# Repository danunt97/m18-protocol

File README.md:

# M18 Akku-Verwaltung

Mit diesem Tool **liest du Milwaukee-M18-Akkus aus, verwaltest sie in einer Datenbank und verfolgst ihre Alterung**.
Das Programm läuft als lokaler Webserver auf dem eigenen PC, ohne Installation und ohne Cloud. Auf Wunsch übernimmt
eine **ESP32-S3-Brücke** das Auslesen per WLAN oder direkt vor Ort mit dem Handy.

Das Projekt baut auf der Protokoll-Forschung von [mnh-jansson/m18-protocol](https://github.com/mnh-jansson/m18-protocol) auf.

## Funktionen

**Akku-Verwaltung (PC, `gui/`)**
- **Auslesen** über einen 3,3-V-USB-Seriell-Adapter oder die ESP32-Brücke. Bekannte Akkus erkennt das Programm automatisch, neue legt es mit einem Klick an.
- **Datenbank (SQLite):** jede Messung mit Zeitstempel, allen Zählern und den rohen Registerwerten.
- **Flottenübersicht:** Zustand, Verlauf, Trend, Zell-Imbalance, Zyklen, Standort, fällige Messungen und offene Warnungen. Die Liste lässt sich filtern und sortieren.
- **Alterung:** Diagramme pro Akku und eine Prognose, wann der Akku schwach wird.
- **Warnungen**, wenn sich ein Akku deutlich verschlechtert: Zustandsabfall, steigende Imbalance, neue Überhitzungs- oder Unterspannungs-Ereignisse, Ladung mit einer Zelle unter 2,5 V.
- **Standort, Kommentar und Gehäuse-Seriennummer** sind editierbar; Akkus lassen sich ausmustern.
- **QR-Etiketten** für P-touch (12–36 mm) und Brother QL (62 mm). Der QR-Code führt direkt zur Akku-Seite, der Code wird offline erzeugt.
- **Berichte:** druckbare A4-Seite bzw. PDF pro Akku, CSV pro Akku oder für die ganze Flotte, Datenbank-Backup.
- **Demo-Modus** mit 8 simulierten Akkus und 2 Jahren Verlauf, ganz ohne Hardware.

**ESP32-S3-Akku-Brücke (`esp32-bridge/`)**
- **Ersetzt den USB-Seriell-Adapter.** Der PC verbindet sich per USB oder WLAN und findet die Brücke im Netz automatisch.
- **Eigene Weboberfläche fürs Handy:**
  - Akku direkt auslesen, mit Zustand, Zellspannungen, Zählern und Daten
  - WLAN-Einrichtung beim Kunden (Captive Portal)
  - Verlauf, Status-LED, Firmware-Update im Browser
- **Messungen offline speichern** (mehrere tausend im Flash) und später **in die PC-Datenbank übernehmen**. Dafür werden die Rohregister gespeichert; eine übernommene Messung ist gleichwertig mit einer am PC.
- **Robust:**
  - Wiederholungen und schneller Abbruch bei gezogenem Akku
  - Watchdog
  - J2 bleibt im Ruhezustand sicher auf Low, damit der Akku keine „Dumb Charge“ zählt
- **Optionaler Passwortschutz.** Einstellungen ändern geht nur nach einem Druck auf die BOOT-Taste.
- **Aufsteckgehäuse zum 3D-Drucken**, Versorgung aus dem Akku, **Energiesparmodus** (Tiefschlaf nach Ruhezeit).
- **Ergebnis auf der LED:** Nach jedem Auslesen leuchtet sie 30 s grün, gelb oder rot, auch wenn der PC ausliest.
- **Firmware im Browser installieren** (ESP Web Tools), ganz ohne Arduino IDE.
- **Cloud (Supabase):** Konto, „Meine Akkus“ mit Verlauf. Jede Messung landet komplett in der Cloud, aus der App oder direkt von der Brücke, wenn sie im WLAN Internet hat.
- **Bluetooth fürs Handy:** Die [Akku-App](https://akkuscan.app/) läuft im Browser (Android: Chrome, iPhone: kostenlose App „Bluefy“).
  Ohne WLAN-Wechsel: Akku auslesen, alle Werte, Verlauf und Protokoll der Brücke. Keine App-Store-App und kein Entwicklerkonto nötig.

**Betrieb auf dem NAS:** Docker-Image mit **automatischem Abgleich**. Die Messungen der Brücken landen von selbst in der Datenbank.

## Bilder

| Akku-Detail mit Alterungsverlauf | Auslesen und Vergleich mit der letzten Messung |
|---|---|
|  |  |
| **QR-Etiketten (P-touch 24 mm)** | **Druckbarer Bericht** |
|  |  |

**ESP32-Brücke am Handy:** WLAN einrichten, Akku auslesen, gespeicherte Messungen

**Messungen der Brücke in die PC-Datenbank übernehmen**

> Alle Bilder stammen aus dem Demo-Modus bzw. aus dem Simulator. Die Messwerte sind simuliert.

## Schnellstart

Du brauchst **Python 3.11 oder neuer**. Weitere Pakete braucht die Demo nicht.

```bash
git clone https://github.com/danunt97/m18-protocol.git
```

```bash
cd m18-protocol
```

```bash
python gui/m18_gui.py --demo
```

Danach öffnet sich der Browser mit http://127.0.0.1:8018. Unter Windows startest du mit `py gui\m18_gui.py --demo`.

**Mit echtem Akku:**

```bash
pip install pyserial
```

```bash
python gui/m18_gui.py
```

Dann **Auslesen** → Adapter wählen → **Verbinden** → **Akku auslesen** → speichern.
Die Datenbank liegt in `data/m18_fleet.db`.

Alle Optionen (`--host 0.0.0.0` für Handy-Scans im WLAN, `--db`, `--port` …) stehen in [gui/README.md](gui/README.md).

**Dauerhaft auf dem NAS / Server (Docker):**

```bash
docker compose up -d
```

Dann ist die Oberfläche unter `http://<NAS-IP>:8018` erreichbar. Die Datenbank liegt in `./data`, und Messungen der ESP32-Brücken
werden **automatisch alle 5 Minuten übernommen**. Das Image (`ghcr.io/danunt97/m18-protocol`) gibt es für amd64 und arm64;
Details stehen in [gui/README.md](gui/README.md#docker).

## Hardware

Es gibt zwei Möglichkeiten, den Akku anzuschließen:

1. **3,3-V-USB-Seriell-Adapter** wie im ursprünglichen Projekt. Verdrahtung und Fehlersuche stehen in [docs/m18-protocol.md](docs/m18-protocol.md).
2. **ESP32-S3 (N16R8) als Brücke.** Das bringt WLAN, Messen ohne PC und eine eigene Weboberfläche. Am bequemsten ist das
   **3D-gedruckte Aufsteckgehäuse**: Es wird wie ein Werkzeug auf den Akku geschoben und versorgt die Elektronik über einen
   Step-down-Wandler aus dem Akku. Druckdateien, Stückliste und Zusammenbau stehen in [hardware/aufsteckgehaeuse/](hardware/aufsteckgehaeuse/README.md).

| Aufsteckgehäuse | Elektronik im Gehäuse |
|---|---|
|  |  |

**Firmware ohne Arduino IDE installieren:** Die Seite **[akkuscan.app/flasher](https://akkuscan.app/flasher/)**
öffnen (Chrome oder Edge), das Board per USB anstecken und auf **Installieren** klicken.

Oder mit der Arduino IDE 2 flashen. Ins Werkzeuge-Menü gehören diese Einstellungen:
- Board: **ESP32S3 Dev Module**
- Flash: **16MB**
- PSRAM: **OPI**
- Partition: **16M Flash (3MB APP/9.9MB FATFS)**
- USB CDC On Boot: **Enabled**

Danach `esp32-bridge/m18_bridge/m18_bridge.ino` hochladen. Alles Weitere zu WLAN-Einrichtung, LED, Passwort und Update
steht in [esp32-bridge/README.md](esp32-bridge/README.md).

> ⚠️ **Sicherung (T 500 mA) direkt hinter B+ einbauen** und den **Step-down vor dem ersten Anschließen auf 5,0 V einstellen.** Solange das Gehäuse steckt, versorgt der Akku die Elektronik.
> Die Brücke schläft deshalb nach 30 min Ruhe (BOOT-Taste weckt sie); nach Gebrauch abziehen.
>
> ⚠️ **Sicherheit:** Arbeiten an Li-Ion-Akkus auf eigene Gefahr. Die ESP32-Brücke kann nur lesen und die
> 20-Zeichen-Notiz im Akku schreiben. Zähler, Kalibrierung oder Firmware des Akkus fasst sie nicht an.

## Wie wird der Zustand bewertet?

Der Akku speichert keinen echten State-of-Health. Die Software **schätzt** ihn aus den Verschleißzählern im Akku:
100 Punkte minus Abzüge für
- Zyklen (entladene Ah ÷ Nennkapazität)
- Zell-Imbalance
- Ladungen mit einer Zelle < 2,5 V
- Überhitzung
- Kalenderalter

Jeder Abzug wird einzeln angezeigt.
Aussagekräftig ist vor allem der **Verlauf über mehrere Messungen**. Details und Warnschwellen findest du in [gui/README.md](gui/README.md).

## Projektstruktur

```
m18.py                  Protokoll und Kommandozeile (aus m18-protocol)
m18_bridge.py           ESP32-Brücke als M18-Objekt (USB/WLAN), Suche, Abgleich
gui/                    Akku-Verwaltung: Webserver, Datenbank, Alterung, QR, Berichte
  m18_gui.py            Start: python gui/m18_gui.py [--demo]
  fleet.py              SQLite, Zustandsschätzung, Warnungen, Trend
  registers.py          Register → Messwerte (Live und Import identisch)
  bridge_import.py      Messungen der Brücke übernehmen
  qrgen.py              QR-Code-Encoder (reines Python)
  static/               Oberfläche (HTML/CSS/JS, ohne Framework)
webble/                 Bluetooth-Adapter: macht die Weboberfläche der Brücke zur Handy-App (akkuscan.app/app/)
supabase/               Cloud-Datenbank (Schema, Zugriffsregeln, Upload-Funktionen)
esp32-bridge/
  m18_bridge/           Arduino-Sketch + reine C++-Header (Protokoll, Auslesen, Speicher)
  test/                 Simulator und Ende-zu-Ende-Tests
hardware/aufsteckgehaeuse/  3D-Druck-Gehäuse (3MF, STL, Fusion 360), Stückliste, Zusammenbau
docs/                   Bilder, ursprüngliche Protokoll-Doku, Register-Tabelle
```

## Tests

Die Tests laufen ohne Hardware: Ein simulierter Akku spricht das echte Protokoll, und der C++-Kern der Firmware wird
auf dem PC mitgetestet. GitHub Actions führt sie bei jedem Push aus und **kompiliert die Firmware für den ESP32-S3**
mit den Arduino-Cores 2.x und 3.x.

```bash
python -m unittest discover -s gui/tests
```

```bash
g++ -std=c++17 -I esp32-bridge/m18_bridge esp32-bridge/test/sim_bridge.cpp -o sim_bridge
```

```bash
./sim_bridge test
```

```bash
python -m unittest esp32-bridge/test/test_bridge.py esp32-bridge/test/test_history.py
```

Die Brücken-Tests über USB brauchen `pyserial`, alles andere nur die Standardbibliothek.

## Grundlage und Hinweise

- Protokoll, Registertabelle und `m18.py` stammen aus [mnh-jansson/m18-protocol](https://github.com/mnh-jansson/m18-protocol)
  und der Community dort. Die ursprüngliche Anleitung liegt in [docs/m18-protocol.md](docs/m18-protocol.md).
- Kein offizielles Milwaukee-Produkt. „Milwaukee“ und „M18“ sind Marken ihrer jeweiligen Inhaber.
- Änderungen stehen im [CHANGELOG](CHANGELOG.md).

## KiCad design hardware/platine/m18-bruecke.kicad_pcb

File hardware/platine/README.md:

# Platine: M18-Brücke mit ESP32-S3 SuperMini

Eigene Leiterplatte für die [Akku-Brücke](../../esp32-bridge/README.md). Die fünf Akkukontakte sitzen direkt auf der Platine. Der SuperMini wird mit seinen mitgelieferten Stiftleisten direkt eingelötet. Der Pegelwandler ist durch zwei kleine Transistorstufen ersetzt, der
Step-down-Wandler durch einen RECOM-Schaltregler. Alles ist von Hand lötbar (SMD ab 0805 / SOT-23 / SMA).

| Oben | Unten (Akkuseite) |
|---|---|
|  |  |

> **Stellen mit ⚠ PRÜFEN** beruhen auf Annahmen, weil Datenblatt, Pinbelegung oder Foto beim Entwurf fehlten.
> Bitte vor der Bestellung der 20 Platinen kontrollieren (Liste ganz unten).

## Eckdaten

| | |
|---|---|
| Größe | **58 × 38 mm**, 2 Lagen, 1,6 mm, 35 µm Kupfer |
| Befestigung | 4 × **M3** (Bohrung 3,2 mm), Mitte 4 mm von den Kanten, Lochabstand **50 × 30 mm** |
| Akkukontakte | 5 × TE **928814-1** (FASTON 6,35 × 0,81 mm) im Raster **5,625 mm** auf der **Unterseite**. Lötstifte am linken Rand, die Messer zeigen unter die Platine, die damit über dem Akku liegt |
| Versorgung | aus dem Akku (B+ 15–21 V) oder über USB-C des SuperMini |
| Ruhestrom aus B+ | nur der Eigenverbrauch des Reglers (R-78E, Wert im Datenblatt nachsehen und am Muster messen) und der Schlafstrom des ESP. Die J2-Stufe zieht im Ruhezustand nichts. |
| Laden | vorbereitet: Lötlöcher CHG+/CHG− für 1,5-mm²-Litze und 6-poliger Steuerstecker, nichts bestückt |

Bezugspunkt aller Maße ist die linke obere Ecke der Draufsicht (x nach rechts = Richtung der Messerspitzen = Einsteckrichtung, y nach unten).

## Akkukontakte

Draufsicht, Lötstifte am linken Rand, Messerspitzen zeigen nach rechts unter die Platine:

| Kontakt | Bauteil | Mitte y | Abstand zum Nachbarn |
|---|---|---|---|
| **B+** | X1 | 7,750 mm | – |
| **J1** | X2 | 13,375 mm | 5,625 mm |
| **M** (Mitte) | X5 | 19,000 mm | 5,625 mm |
| **J2** | X3 | 24,625 mm | 5,625 mm |
| **B−** | X4 | 30,250 mm | 5,625 mm |

- Von oben in Einsteckrichtung gesehen (Spitzen zeigen von dir weg): **links B+, J1, M, J2, rechts B−**. In der Draufsicht oben ist deshalb B+.
- Raster 5,625 mm von Mitte zu Mitte, wie in der Skizze des Printables-Modells „Milwaukee M18 All Pins“. Die Platinenmitte (y = 19) ist der mittlere Kontakt.
- Der **mittlere Kontakt M** (X5) ist mit nichts verbunden, er führt nur auf das Lötfeld **TP3** zwischen seinen beiden Stiften.
  Welche Funktion er im Akku hat, ist noch unbekannt. Über TP3 lässt er sich später mit einem Draht anschließen.
- Die Lötstifte liegen bei x = 1,74 und 6,82 mm, das Messer reicht von x = 2,3 bis 18,3 mm (Spitze rechts). Es ist 6,35 mm hoch und steht senkrecht auf der Unterseite.
  Die beiden Stifte eines Messers sind nur über das Messer selbst verbunden (im Footprint als Jumper-Pads eingetragen).
- Unter den Messern sind auf der Unterseite keine Leiterbahnen, Durchkontaktierungen und Kupferflächen erlaubt (Sperrflächen),
  damit kein Messer nur durch den Lötstopplack getrennt auf einem fremden Netz aufliegt.
  Oben über den Messern sitzen nur SMD-Teile, die Unterseite bleibt dort glatt.
- Oben zwischen den Messern sitzt die Eingangsstufe: F1, D1, C1 und D2. Die Signale J1 und J2 wechseln deshalb gleich neben
  ihren Lötstiften über ein Via auf die Unterseite und laufen dort im freien Kanal zwischen den Messern nach rechts.
- ⚠ **PRÜFEN:** Ohne TE-Datenblatt stammen Lochbild und 3D-Modell aus dem SamacSys-Modell in `quellen/LIB_928814-1`.
  Höhe und Lage des Messers am ersten Muster mit dem Akku ausprobieren, bevor das Gehäuse fertig konstruiert wird.

## Pinbelegung ESP32-S3 SuperMini

Draufsicht. Der SuperMini sitzt rechts unten, **USB-C zeigt zur unteren Platinenkante** (Seite B−). Von oben in Einsteckrichtung gesehen ist das rechts,
so bleibt die Buchse beim Aufstecken frei und läuft nicht gegen den Akku. Die Modulkante liegt bündig mit der Platinenkante, die Buchse steht ~1 mm über.
Reihenabstand 15,24 mm, je 9 Pins, Pin 1 und 10 an der USB-Seite (y = 35,8).

| Pin | Rechte Reihe (x = 48,80) | Funktion | Linke Reihe (x = 33,56) | Funktion |
|---|---|---|---|---|
| 1 / 10 (USB-Seite) | GPIO43 (U0TXD) | frei | 5V | Versorgung über D3 (B140) aus dem Regler |
| 2 / 11 | GPIO44 (U0RXD) | frei | GND | Masse = B− |
| 3 / 12 | GPIO1 | frei | 3V3 | Versorgung OLED, Pull-ups, Steuerstecker |
| 4 / 13 | GPIO2 | frei | GPIO13 | RGB-LED **rot** (Q5 → Pad 1) |
| 5 / 14 | GPIO3 (Strapping) | frei | GPIO12 | RGB-LED **blau** (Q6 → Pad 4) |
| 6 / 15 | GPIO4 | **Reserve** → Steuerstecker Pin 6 | GPIO11 | RGB-LED **grün** (Q7 → Pad 3) |
| 7 / 16 | GPIO5 | **CHG_EN** → Steuerstecker Pin 5 | GPIO10 | frei |
| 8 / 17 | GPIO6 | **RX** ← J1-Stufe | GPIO9 | **SCL** (4,7 kΩ Pull-up) |
| 9 / 18 | GPIO7 | **TX** → J2-Stufe | GPIO8 | **SDA** (4,7 kΩ Pull-up) |

- Onboard-WS2812 des SuperMini: GPIO48. BOOT-Taste: GPIO0.
- Die Pinbelegung stammt von [espboards.dev](https://espboards.dev/esp32/esp32-s3-super-mini/) und stimmt mit dem Pinout-Bild
  des bestellten Boards überein (Heemol ESP32-S3 Mini, Aufdruck „Super Mini ESP32-S3 HW-747“).
  ⚠ **PRÜFEN:** Den Reihenabstand von 15,24 mm (Board 18 mm breit) habe ich angenommen. Am Board nachmessen, bevor die Platinen bestellt werden.

## Steckverbinder und Lötpunkte

| Bauteil | Pin 1 → n | Hinweis |
|---|---|---|
| **J1** OLED, Buchse 1×4 (Harwin M20-7820442) | **GND, VCC (3V3), SCL, SDA** | Von oben gesehen von links nach rechts, Pin 1 (GND) ist das eckige Pad links. Passt zum QIQIAZI-0,96″-Modul (Aufdruck GND VCC SCL SDA). Das Display schaut über den SuperMini. |
| **J2** Lade-Steuerung, Stiftleiste 1×6 | 3V3, GND, SDA, SCL, CHG_EN, Reserve (GPIO4) | **nicht bestücken** (DNP) |
| **TP1** CHG+ | B+ direkt am Akkukontakt, **vor** der Sicherung | Lötloch 1,8 mm, für ~5 A |
| **TP2** CHG− | B− direkt am Akkukontakt | Lötloch 1,8 mm, für ~5 A |

Die Ladeleitungen sind breit ausgeführt:
- **B+ → CHG+:** 2,5 mm auf der Oberseite (CHG+ liegt oben bei B+).
- **B− → CHG−:** 3 mm auf der Oberseite plus Massefläche (CHG− liegt unten bei B−).

Der Ladestrom fließt **nicht** durch F1. Eine spätere Ladeplatine braucht deshalb ihre eigene Absicherung.

## Schaltung

Schaltplan: [`m18-bruecke.kicad_sch`](m18-bruecke.kicad_sch), als PDF in [`fertigung/m18-bruecke-schaltplan.pdf`](fertigung/m18-bruecke-schaltplan.pdf).

**Versorgung**
- **Pfad:** B+ → **F1** 500 mA träge (Littelfuse 0452.500MRL) → **D1** B1100 (Verpolschutz) → VBAT.
- **Schutz und Puffer an VBAT:** TVS **D2** SMBJ24A und **C1** 4,7 µF/50 V.
- **Regler:** **U2** R-78E5.0-0.5 macht aus VBAT 5 V (C2 10 µF). **D3** B140 führt die 5 V zum 5V-Pin des SuperMini.
- **USB und Regler gleichzeitig:** D3 verhindert, dass USB in den Regler zurückspeist. Der Regler liefert hinter D3 nur ~4,6 V und
  liegt damit unter der USB-Spannung, er speist also auch nicht in den PC. Das Arbeiten gegeneinander, das beim DevKit die Lötbrücke „IN-OUT“
  verursacht hat, fällt weg.

**J2 – Senden** (Q1 MMBT3904, Q2 MMBT3906, nicht invertierend: TX high → J2 = B+)
- **Ansteuerung:** GPIO7 → R1 2,2 kΩ → Basis Q1. **R2 4,7 kΩ** zieht die Basis nach GND. Auch mit dem internen Pull-up des ESP
  beim Booten bleibt die Basis unter 0,3 V, J2 bleibt also low.
- **High-Side-Schalter:** Q1 schaltet über R4 10 kΩ die Basis von Q2. R3 10 kΩ hält Q2 gesperrt. Q2 legt B+ (VBAT) über **R5 1 kΩ** an J2.
- **Low-Pegel:** **R6 10 kΩ** zieht J2 nach B−, wenn Q2 aus ist.
- **Strom:** Im Ruhezustand fließt kein Strom aus B+. Bei J2 = high sind es ca. 4 mA, davon 2 mA in die Basis von Q2 und ~2 mA durch R6.
- Die Firmware bleibt gleich: Der UART-TX ist im Ruhezustand invertiert (= low), genau wie mit dem Pegelwandler.

**J1 – Empfangen** (Q3, Q4 MMBT3904 wie im Spud-Isolator `docs/spud_isolator.png`, nicht invertierend)
- J1 → R7 15 kΩ → Basis Q3, R8 100 kΩ nach GND (nur damit ein offener Kontakt nicht schwebt).
- Q3 zieht die Basis von Q4 auf Low, R9 15 kΩ Pull-up auf 3,3 V. Q4 zieht RX (GPIO6) auf Low, R10 10 kΩ Pull-up auf 3,3 V.

**RGB-LED** (5 mm, gemeinsame Anode; bestellt: Lumetheus RGB, Pinfolge R, A, G, B)
- Grün und Blau brauchen ~3,2 V und gehen deshalb nicht an 3,3 V. Die Anode liegt an +5 V, jede Kathode an einem MMBT3904 (Q5–Q7, Basis 2,2 kΩ).
- Vorwiderstände: rot 270 Ω, grün/blau 150 Ω, das ergibt ca. 7–9 mA bei voller Helligkeit.
- Lage: links unten neben dem Regler, außerhalb des Displays und vor keinem Stecker. Die Treiber Q5–Q7 und die Widerstände sitzen unter dem SuperMini.
- Die Firmware zeigt auf der LED dieselben Farben wie auf der WS2812.
- Pinfolge: Rot kommt ins eckige Pad 1, die Anode (längster Pin) in Pad 2, dann Grün (Pad 3, GPIO11) und Blau (Pad 4, GPIO12).
  So ist die Lumetheus-LED belegt, und so sind Schaltplan und Firmware ausgelegt. Eine Dialight 521-8559F hat Blau und Grün vertauscht (R, A, B, G).
  Mit ihr in `m18_bridge.ino` `PIN_RGB_G` und `PIN_RGB_B` tauschen.
- Hinweis: Die Basen von Q5–Q7 haben keinen Pull-down. Beim Einschalten kann die LED kurz schwach glimmen, bis die Firmware die Pins setzt.
  Im Tiefschlaf hält die Firmware die Pins auf Low.

## Firmware

Variante `BOARD_SUPERMINI` (TX = GPIO7, RX = GPIO6, RGB-LED an GPIO13/12/11, CHG_EN = GPIO5 low, 4 MB Flash, PSRAM quad),
siehe [esp32-bridge/README.md](../../esp32-bridge/README.md#variante-eigene-platine-mit-esp32-s3-supermini).
Im [Web-Flasher](https://danunt97.github.io/m18-protocol/) gibt es dafür einen eigenen Knopf „ESP32-S3 SuperMini“.

## Fertigung

| Datei | Inhalt |
|---|---|
| [`fertigung/m18-bruecke-gerber.zip`](fertigung/m18-bruecke-gerber.zip) | Gerber (X2) und Bohrdateien (Excellon, mm, PTH/NPTH getrennt) – so beim Leiterplattenhersteller hochladen |
| `fertigung/gerber/` | dieselben Dateien ausgepackt, dazu die Bohrpläne als PDF |
| [`fertigung/m18-bruecke-bestellliste.xlsx`](fertigung/m18-bruecke-bestellliste.xlsx) | Stückliste für 20 Platinen: Mouser-Teile mit Hersteller- und Mouser-Nummern, dazu SuperMini, RGB-LED und OLED von Amazon (Blatt „Sonstiges“) |
| `fertigung/m18-bruecke-bestueckung-oben.pdf` / `-unten.pdf` | Bestückungsplan (alle Referenzen, auch die, die im Bestückungsdruck keinen Platz haben) |
| `fertigung/m18-bruecke-schaltplan.pdf` | Schaltplan |

Einstellungen beim Hersteller: 2 Lagen, 1,6 mm FR4, 1 oz Kupfer, HASL oder ENIG. Minimale Werte im Design: Leiterbahn 0,3 mm,
Abstand 0,2 mm, Via 0,7/0,35 mm, Kupfer zum Rand 0,4 mm, Lötstopp-Freistellung 0,05 mm, Vias abgedeckt.

**JLC-DFM:** Siebdruck liegt nicht über Bohrungen (Via-Sperrflächen entlang aller Bestückungsdruck-Linien). Der Bestückungsdruck wird mit 0,22 mm
Freistellung um die Pads exportiert, Siebdruck näher als 0,15 mm an der Lacköffnung fällt dadurch weg (`neu_routen.sh`).
Die Meldung „THT zu SMD“ (Abstand Lötloch zu SMD-Pad < 1 mm, v. a. unter dem SuperMini und an den Akkukontakten) betrifft nur
maschinelles Wellen-/Selektivlöten und ist bei Handbestückung bedeutungslos.

**Schaltplan:** in Funktionsblöcke gegliedert (Akkuanschluss, Versorgung, SuperMini, RGB-LED, J2 senden, J1 empfangen, OLED/Lade-Steuerung),
GND/+5V/+3V3 als Versorgungssymbole, Verbindungen zwischen den Blöcken über Netznamen.

**Prüfung:** ERC 0 Fehler/Warnungen. DRC (alle Schweregrade) 0 Verstöße, 0 offene Verbindungen, Schaltplan und Platine stimmen überein.

### Bestücken

1. SMD-Teile oben (Widerstände, Transistoren, Dioden, C1/C2, F1). **Die Teile unter dem SuperMini** (Q3–Q7, R7–R10, R16–R18)
   müssen vor dem SuperMini drauf und kontrolliert sein, später kommt man nicht mehr heran.
2. R-78E (U2) und die OLED-Buchse.
3. SuperMini mit seinen **mitgelieferten Stiftleisten direkt einlöten** (kein Sockel). Die Stiftleisten zuerst in die Platine stecken,
   SuperMini auflegen, oben und unten verlöten. Der Kunststoffhalter der Stiftleiste (~2,5 mm) ist der Abstand zu den SMD-Teilen darunter.
   Am besten vorher die Firmware über den Web-Flasher aufspielen und den SuperMini einmal testen.
4. RGB-LED: Die Pads sind versetzt. Die vier Beinchen leicht abwechselnd nach vorne und hinten biegen. Der lange Anschluss (Anode) gehört an Pin 2.
5. Zuletzt die fünf Akkukontakte von **unten** einsetzen und oben verlöten. Die Messer müssen senkrecht stehen.
6. Erster Test am Netzteil (12–20 V an B+/B−, Strom auf 100 mA begrenzen): am 5V-Pin ~4,6 V, die LED zeigt den WLAN-Status.
   Am besten schon nach Schritt 2 (vor dem SuperMini) einmal die 4,6 V an den Lötaugen von Pin 5V prüfen.
7. Mit Akku prüfen: **J2 gegen B− unter 1 V**.

## ⚠ Vor der Bestellung prüfen

1. **Reihenabstand des SuperMini** (15,24 mm) am echten Board nachmessen. Die Pinbelegung ist geprüft.
2. **Kontaktreihenfolge**: links B+, J1, M, J2, rechts B−, von oben in Einsteckrichtung gesehen. Sonst sind B+ und B− vertauscht.
   D1 schützt dann zwar die Elektronik, die Brücke funktioniert aber nicht.
3. **TE 928814-1**: Datenblatt fehlte, Maße aus dem SamacSys-Modell. Lochdurchmesser 1,45 mm und Messerhöhe prüfen.
4. **Mengen im Mouser-Warenkorb** gegen die Bestellliste prüfen (Bedarf für 20 Platinen).
5. **J2-Pegel**: R6 10 kΩ zieht J2 im Ruhezustand nach B−. Falls der Akku J2 intern stark nach oben zieht, R6 verkleinern (z. B. 4,7 kΩ). Am Muster messen.
6. **Höhe**: R-78E ~10 mm, SuperMini ~2,5 mm über der Platine (plus USB-C-Buchse), OLED-Buchse 8,5 mm, RGB-LED 8,6 mm. Für das neue Gehäuse aus dem 3D-Modell (`m18-bruecke.kicad_pcb`, 3D-Ansicht) übernehmen.

## Dateien

| Datei | Inhalt |
|---|---|
| `m18-bruecke.kicad_pro/.kicad_sch/.kicad_pcb` | KiCad-10-Projekt |
| `lib/m18.kicad_sym`, `lib/m18.pretty`, `lib/3d` | Projektbibliothek: SuperMini-Lochbild (2 × 9, Footprint „ESP32-S3_SuperMini_Sockel“), TE 928814-1, Harwin-Buchse, RGB-LED (KiCad-Footprint ohne den Silk-Bogen an Pad 4), Lötloch (THT) und SMD-Lötfeld |
| `quellen/` | Herstellerbibliotheken (TE 928814-1, Dialight 521-8559F, Harwin M20-7820442) |
| `tools/` | Skripte, mit denen die Platine entstanden ist (KiCad-Python). **`neu_routen.sh`** baut alles neu auf: Netze und Felder aus dem Schaltplan, Bauteillage (`lage.py`), feste Leitungen (`vorrouten.py`: Akkuleitungen, J1/J2 über Vias in die Kanäle zwischen den Messern, LED-Kathoden unten durch die Stiftreihe, SDA zwischen den Steckern), Sperrflächen (`sperrflaechen.py`: unter den Messern, Rand, keine Vias unter Siebdruck), Freerouting, GND-Flächen und Sperrflächen (`flaechen.py`), Bestückungsdruck (`beschriftung.py`), ERC/DRC, Gerber, PDFs, Bilder und Bestellliste. KiCad vorher schließen. Dazu: `schaltplan.py` zeichnet den Schaltplan (Lage, Leitungen, Texte) neu, `netze_umbenennen.py` zieht danach geänderte Netznamen in die Platine nach, `fp_aktualisieren.py` übernimmt geänderte Grafik der Projekt-Footprints. |

Geroutet wurde mit [Freerouting](https://github.com/freerouting/freerouting) 2.2.4 (braucht Java 25, erwartet unter `~/.kicad-mcp/`).
Die Akkuleitungen sind von Hand gelegt und gesperrt. Wer in KiCad von Hand weiterarbeitet, braucht die Skripte nicht. `neu_routen.sh` würde Handänderungen an Leiterbahnen überschreiben.

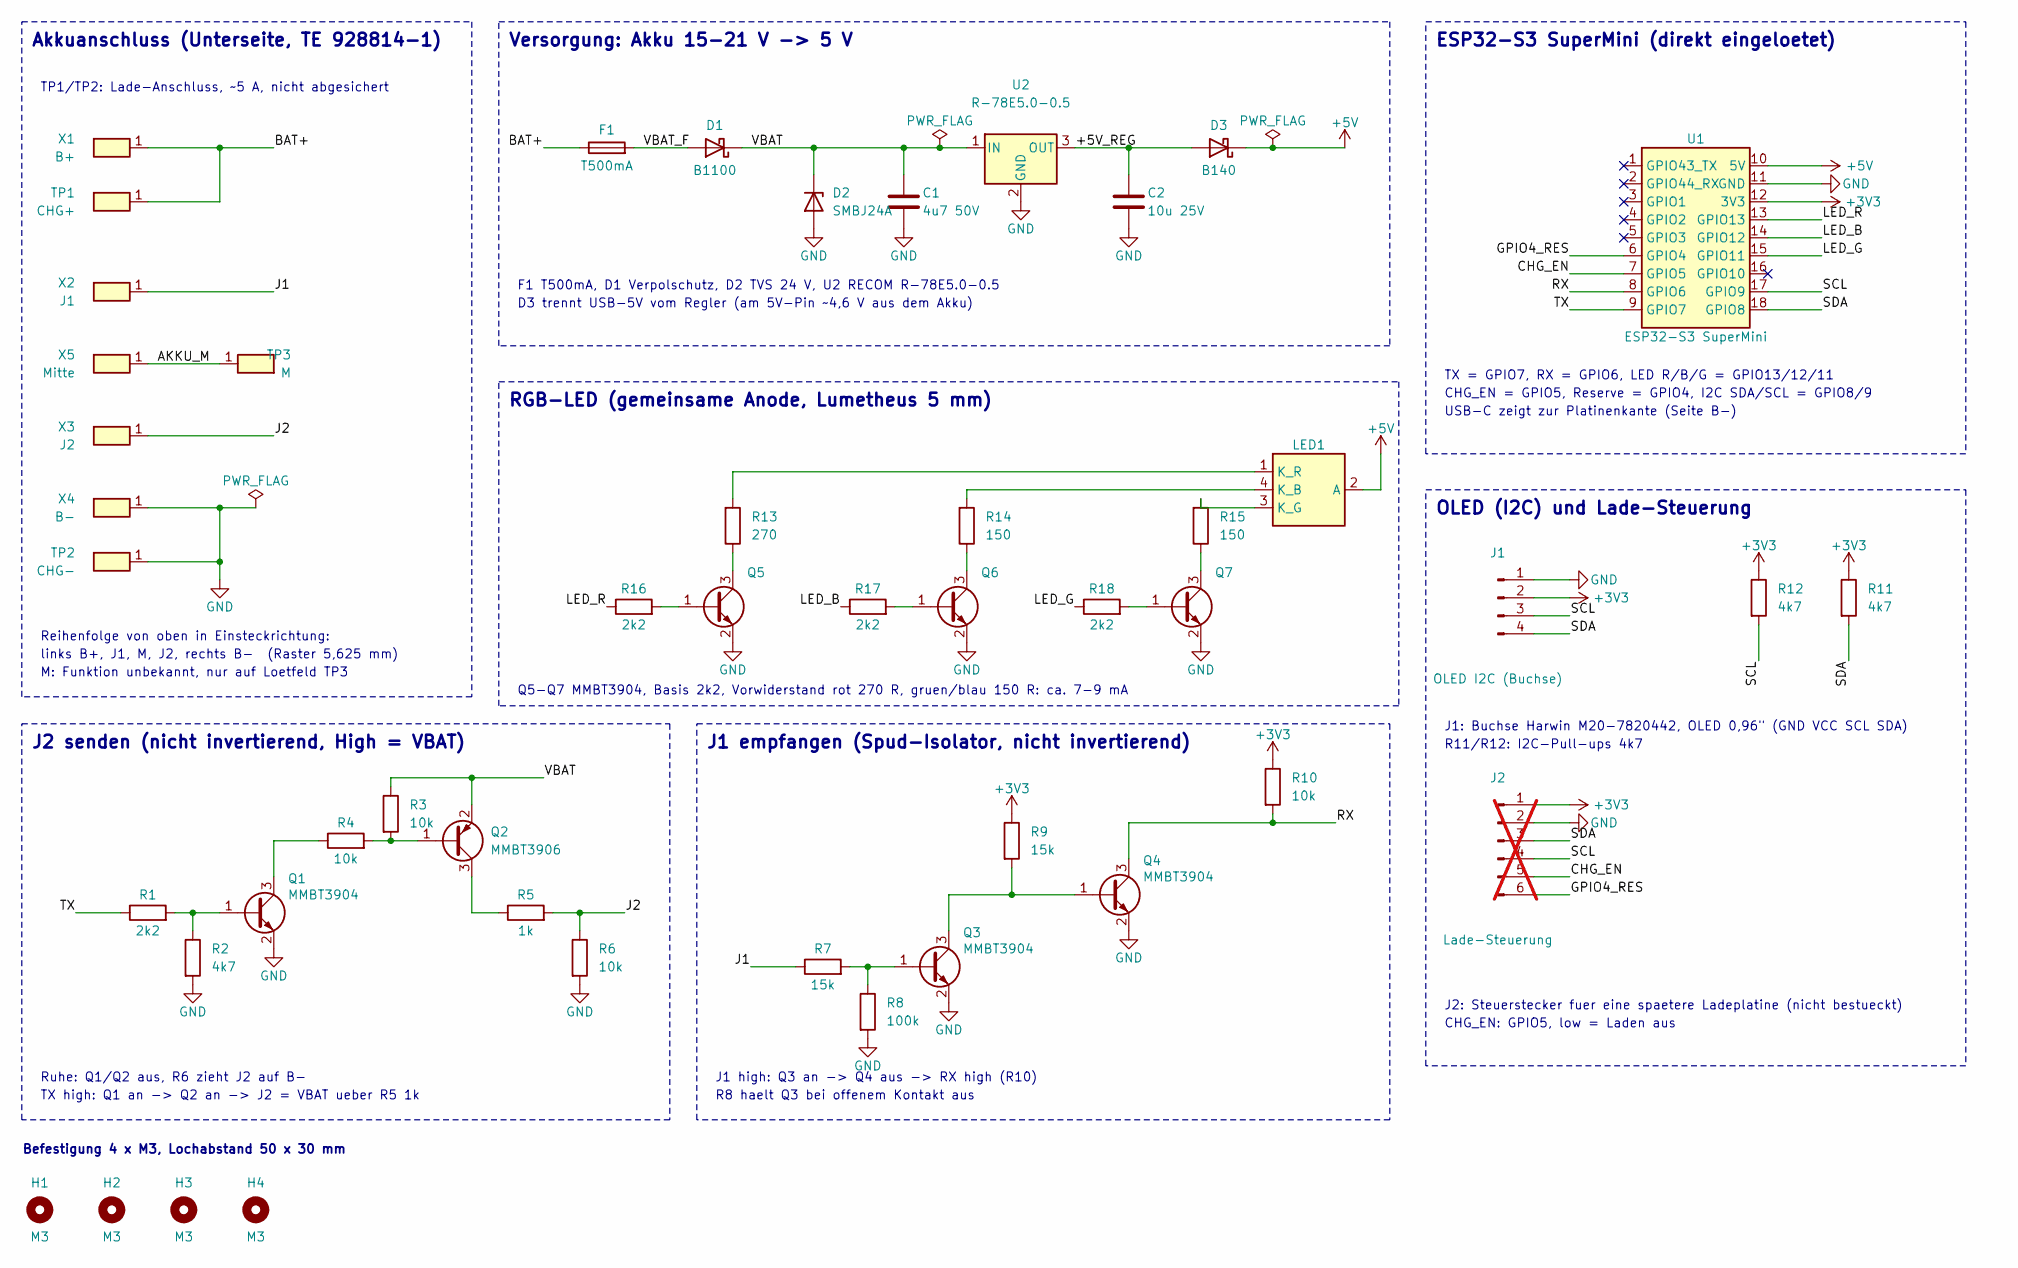
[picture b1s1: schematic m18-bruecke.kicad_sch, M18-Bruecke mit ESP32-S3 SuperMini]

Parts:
C1: 4u7 50V; C_1206_3216Metric_Pad1.33x1.80mm_HandSolder; MPN GJ831CR71H475KA12L; Mouser 81-GJ831CR71H475KA2L
C2: 10u 25V; C_1206_3216Metric_Pad1.33x1.80mm_HandSolder; MPN CC1206KKX7R8BB106; Mouser 603-CC126KKX7R8BB106
D1: B1100; D_SMA_Handsoldering; MPN B1100-13-F; Mouser 621-B1100-F
D2: SMBJ24A; D_SMB_Handsoldering; MPN SMBJ24A; Mouser 576-SMBJ24A
D3: B140; D_SMA_Handsoldering; MPN B140-13-F; Mouser 621-B140-F
F1: T500mA; Fuse_Littelfuse-NANO2-451_453; MPN 0452.500MRL; Mouser 576-0452.500MRL
H1, H2, H3, H4: M3; MountingHole_3.2mm_M3
J1: OLED I2C (Buchse); Harwin_M20-7820442; MPN M20-7820442; Mouser 855-M20-7820442
J2: Lade-Steuerung; PinHeader_1x06_P2.54mm_Vertical; MPN 61300611121; Mouser 710-61300611121; not fitted
LED1: RGB 5mm gem. Anode (R,A,G,B); LED_D5.0mm-4_RGB_Staggered_Pins_m18; MPN 2001001007
Q1, Q3, Q4, Q5, Q6, Q7: MMBT3904; SOT-23_Handsoldering; MPN MMBT3904LT1G; Mouser 863-MMBT3904LT1G
Q2: MMBT3906; SOT-23_Handsoldering; MPN MMBT3906LT1G; Mouser 863-MMBT3906LT1G
R1, R16, R17, R18: 2k2; R_0805_2012Metric_Pad1.20x1.40mm_HandSolder; MPN RC0805FR-072K2L; Mouser 603-RC0805FR-072K2L
R2, R11, R12: 4k7; R_0805_2012Metric_Pad1.20x1.40mm_HandSolder; MPN RC0805FR-074K7L; Mouser 603-RC0805FR-074K7L
R3, R4, R6, R10: 10k; R_0805_2012Metric_Pad1.20x1.40mm_HandSolder; MPN RC0805FR-0710KL; Mouser 603-RC0805FR-0710KL
R5: 1k; R_0805_2012Metric_Pad1.20x1.40mm_HandSolder; MPN RC0805FR-071KL; Mouser 603-RC0805FR-071KL
R7, R9: 15k; R_0805_2012Metric_Pad1.20x1.40mm_HandSolder; MPN RC0805FR-0715KL; Mouser 603-RC0805FR-0715KL
R8: 100k; R_0805_2012Metric_Pad1.20x1.40mm_HandSolder; MPN RC0805FR-07100KL; Mouser 603-RC0805FR-07100KL
R13: 270; R_0805_2012Metric_Pad1.20x1.40mm_HandSolder; MPN RC0805FR-07270RL; Mouser 603-RC0805FR-07270RL
R14, R15: 150; R_0805_2012Metric_Pad1.20x1.40mm_HandSolder; MPN RC0805FR-07150RL; Mouser 603-RC0805FR-07150RL
TP1: CHG+; Loetpad_Kabel_1.8mm
TP2: CHG-; Loetpad_Kabel_1.8mm
TP3: M; Loetpad_SMD_1.6x2.0mm
U1: ESP32-S3 SuperMini; ESP32-S3_SuperMini_Sockel; MPN ESP32-S3 SuperMini
U2: R-78E5.0-0.5; Converter_DCDC_RECOM_R-78E-0.5_THT; MPN R-78E5.0-0.5; Mouser 919-R-78E5.0-0.5
X1: B+; TE_928814-1; MPN 928814-1; Mouser 571-928814-1
X2: J1; TE_928814-1; MPN 928814-1; Mouser 571-928814-1
X3: J2; TE_928814-1; MPN 928814-1; Mouser 571-928814-1
X4: B-; TE_928814-1; MPN 928814-1; Mouser 571-928814-1
X5: Mitte; TE_928814-1; MPN 928814-1; Mouser 571-928814-1

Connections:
+3V3: J1.2, J2.1, R9.1, R10.1, R11.1, R12.1, U1.12 (3V3)
+5V: D3.1 (K), LED1.2 (A), U1.10 (5V)
/+5V_REG: C2.1, D3.2 (A), U2.3 (OUT)
/AKKU_M: TP3.1, X5.1
/BAT+: F1.1, TP1.1, X1.1
/CHG_EN: J2.5, U1.7 (GPIO5)
/GPIO4_RES: J2.6, U1.6 (GPIO4)
/J1: R7.1, X2.1
/J2: R5.2, R6.1, X3.1
/LED_B: R17.1, U1.14 (GPIO12)
/LED_G: R18.1, U1.15 (GPIO11)
/LED_R: R16.1, U1.13 (GPIO13)
/RX: Q4.3 (C), R10.2, U1.8 (GPIO6)
/SCL: J1.3, J2.4, R12.2, U1.17 (GPIO9)
/SDA: J1.4, J2.3, R11.2, U1.18 (GPIO8)
/TX: R1.1, U1.9 (GPIO7)
/VBAT: C1.1, D1.1 (K), D2.1 (K), Q2.2 (E), R3.1, U2.1 (IN)
/VBAT_F: D1.2 (A), F1.2
GND: C1.2, C2.2, D2.2 (A), J1.1, J2.2, Q1.2 (E), Q3.2 (E), Q4.2 (E), Q5.2 (E), Q6.2 (E), Q7.2 (E), R2.2, R6.2, R8.2, TP2.1, U1.11 (GND), U2.2 (GND), X4.1
unnamed: LED1.4 (K_B), R14.2
unnamed: LED1.3 (K_G), R15.2
unnamed: LED1.1 (K_R), R13.2
unnamed: Q1.1 (B), R1.2, R2.1
unnamed: Q1.3 (C), R4.1
unnamed: Q2.1 (B), R3.2, R4.2
unnamed: Q2.3 (C), R5.1
unnamed: Q3.1 (B), R7.2, R8.1
unnamed: Q3.3 (C), Q4.1 (B), R9.2
unnamed: Q5.1 (B), R16.2
unnamed: Q5.3 (C), R13.1
unnamed: Q6.1 (B), R17.2
unnamed: Q6.3 (C), R14.1
unnamed: Q7.1 (B), R18.2
unnamed: Q7.3 (C), R15.1

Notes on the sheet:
Akkuanschluss (Unterseite, TE 928814-1)
Reihenfolge von oben in Einsteckrichtung:
links B+, J1, M, J2, rechts B- (Raster 5,625 mm)
M: Funktion unbekannt, nur auf Loetfeld TP3
TP1/TP2: Lade-Anschluss, ~5 A, nicht abgesichert
Versorgung: Akku 15-21 V -> 5 V
F1 T500mA, D1 Verpolschutz, D2 TVS 24 V, U2 RECOM R-78E5.0-0.5
D3 trennt USB-5V vom Regler (am 5V-Pin ~4,6 V aus dem Akku)
ESP32-S3 SuperMini (direkt eingeloetet)
TX = GPIO7, RX = GPIO6, LED R/B/G = GPIO13/12/11
CHG_EN = GPIO5, Reserve = GPIO4, I2C SDA/SCL = GPIO8/9
USB-C zeigt zur Platinenkante (Seite B-)
RGB-LED (gemeinsame Anode, Lumetheus 5 mm)
Q5-Q7 MMBT3904, Basis 2k2, Vorwiderstand rot 270 R, gruen/blau 150 R: ca. 7-9 mA
J2 senden (nicht invertierend, High = VBAT)
Ruhe: Q1/Q2 aus, R6 zieht J2 auf B-
TX high: Q1 an -> Q2 an -> J2 = VBAT ueber R5 1k
J1 empfangen (Spud-Isolator, nicht invertierend)
J1 high: Q3 an -> Q4 aus -> RX high (R10)
R8 haelt Q3 bei offenem Kontakt aus
OLED (I2C) und Lade-Steuerung
J1: Buchse Harwin M20-7820442, OLED 0,96" (GND VCC SCL SDA)
R11/R12: I2C-Pull-ups 4k7
J2: Steuerstecker fuer eine spaetere Ladeplatine (nicht bestueckt)
CHG_EN: GPIO5, low = Laden aus
Befestigung 4 x M3, Lochabstand 50 x 30 mm

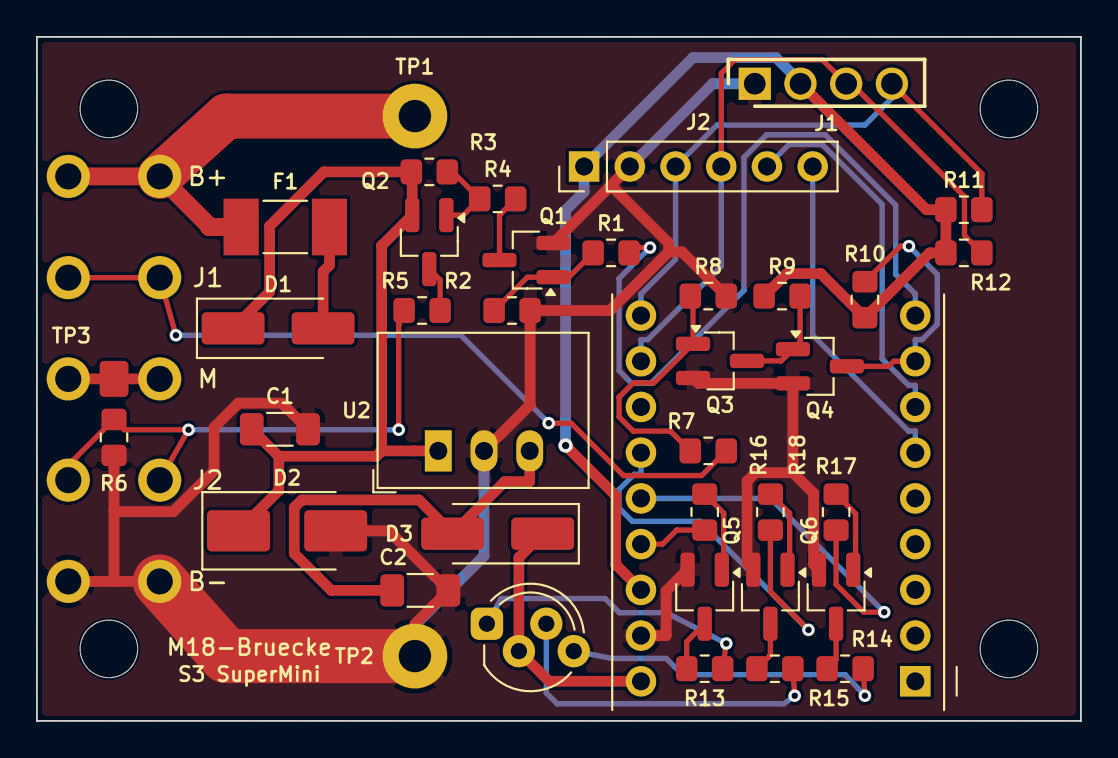
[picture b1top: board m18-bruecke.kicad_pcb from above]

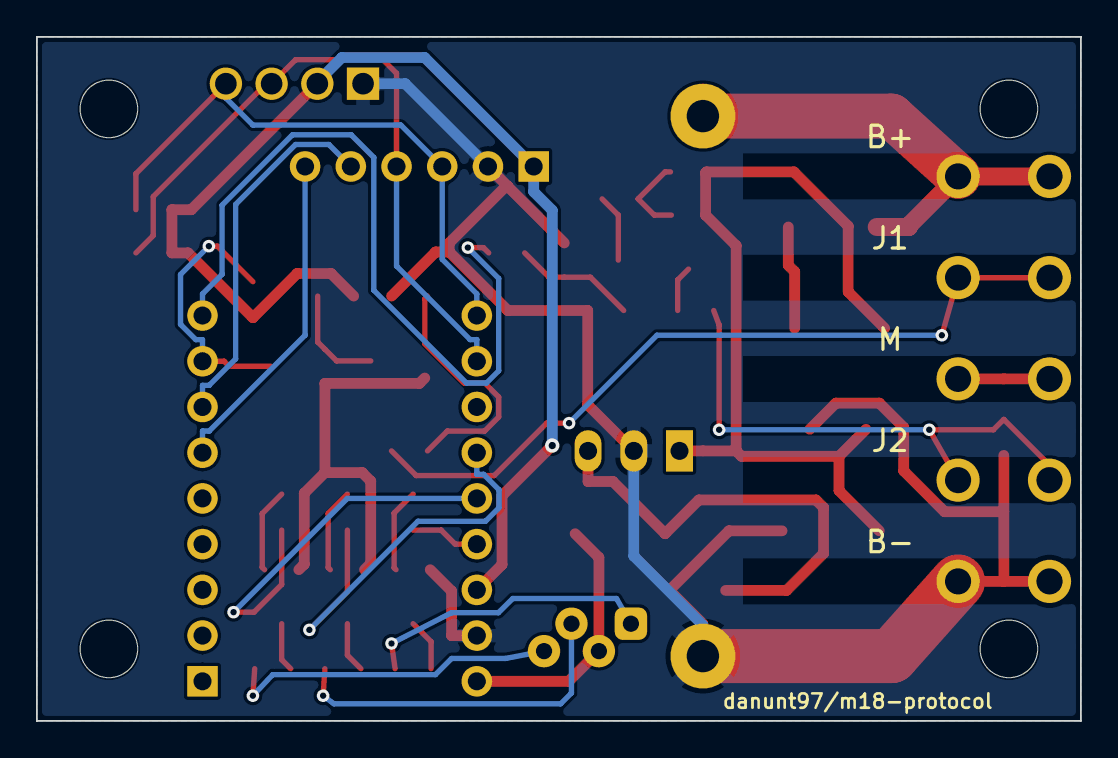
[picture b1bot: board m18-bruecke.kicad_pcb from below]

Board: 2 copper layers, 58.0 x 38.0 mm, 48 parts (5 on the bottom side), 34 nets.

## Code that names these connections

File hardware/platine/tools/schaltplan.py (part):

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wire(pin('TP1','1'),(40.64,38.1),(40.64,30.48)); junction((40.64,30.48))
place('X2',K_X,50.8,fields=KF); wire(pin('X2','1'),(48.26,50.8)); label('J1',(48.26,50.8))
place('X5',K_X,60.96,fields=KF); place('TP3',45.72,60.96,180,fields={'Reference':(5.08,-1.27,'left'),'Value':(5.08,1.27,'left')})
wire(pin('X5','1'),pin('TP3','1')); label('AKKU_M',(31.75,60.96))
place('X3',K_X,71.12,fields=KF); wire(pin('X3','1'),(48.26,71.12)); label('J2',(48.26,71.12))
place('X4',K_X,81.28,fields=KF); place('TP2',K_X,88.9,fields=KF)
wire(pin('X4','1'),(40.64,81.28),(40.64,91.44)); wire(pin('TP2','1'),(40.64,88.9)); junction((40.64,88.9)); gnd((40.64,91.44))
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YV=30.48
label('BAT+',(86.36,YV),180); place('F1',95.25,YV,90,fields=R_H); wire((86.36,YV),pin('F1','1'))
place('D1',110.49,YV,180,fields={'Reference':(0,-3.175),'Value':(0,3.175)})
wire(pin('F1','2'),pin('D1','2')); label('VBAT_F',(100.33,YV))
place('D2',124.46,38.1,270,fields={'Reference':(2.54,-1.27,'left'),'Value':(2.54,1.27,'left')})
place('C1',137.16,38.1,0,fields=R_V)
place('U2',153.67,YV,0,fields={'Reference':(0,-8.89),'Value':(0,-6.35)})
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UX,UY=248.92,43.18
place('U1',UX,UY,0,fields={'Reference':(0,-13.97),'Value':(0,13.97)})
L=7.62
left={'6':'GPIO4_RES','7':'CHG_EN','8':'RX','9':'TX'}
for n in [str(i) for i in range(1,10)]:
    p=pin('U1',n)
    if n in left: wire(p,(p[0]-L,p[1])); label(left[n],(p[0]-L,p[1]),180)
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    elif n=='11': wire(p,e); power('GND',e,90)
    elif n=='12': wire(p,e); power('+3V3',e,270)
    else: nc(p)
text('TX = GPIO7, RX = GPIO6, LED R/B/G = GPIO13/12/11',213.36,63.5,1.27)
text('CHG_EN = GPIO5, Reserve = GPIO4, I2C SDA/SCL = GPIO8/9',213.36,66.04,1.27)
text('USB-C zeigt zur Platinenkante (Seite B-)',213.36,68.58,1.27)

# ================================================================ 4) RGB-LED
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    place(r,x,93.98,0,fields=R_V); power('+3V3',pin(r,'1'))
    bt=pin(r,'2'); wire(bt,(bt[0],bt[1]+5.08)); label(nm,(bt[0],bt[1]+5.08),270)
text('R11/R12: I2C-Pull-ups 4k7',213.36,115.57,1.27)
conn('J2',220.98,128.27,{'1':'+3V3','2':'GND','3':'SDA','4':'SCL','5':'CHG_EN','6':'GPIO4_RES'},'Lade')
text('J2: Steuerstecker fuer eine spaetere Ladeplatine (nicht bestueckt)',213.36,152.4,1.27)
text('CHG_EN: GPIO5, low = Laden aus',213.36,154.94,1.27)

# ================================================================ 8) Befestigung
box(212.09,163.83,220.98,163.83+0.01,'')  # Platzhalter (wird entfernt)
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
